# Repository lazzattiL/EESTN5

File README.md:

This repository is for any project I'll make during my studying period at E.E.S.T. N° 5 "2 de Abril". 
Triatlon robot will be added at some point of the competition to avoid others from stealing our code.
The following link is from the RadioFM project tinkercad model: https://www.tinkercad.com/things/35Wzm8qwek5-radio-fm-with-oled-display?sharecode=DG-30qTOyq2ryuBf1aKIaMlBNb57CfATmdjBPJIcnF0

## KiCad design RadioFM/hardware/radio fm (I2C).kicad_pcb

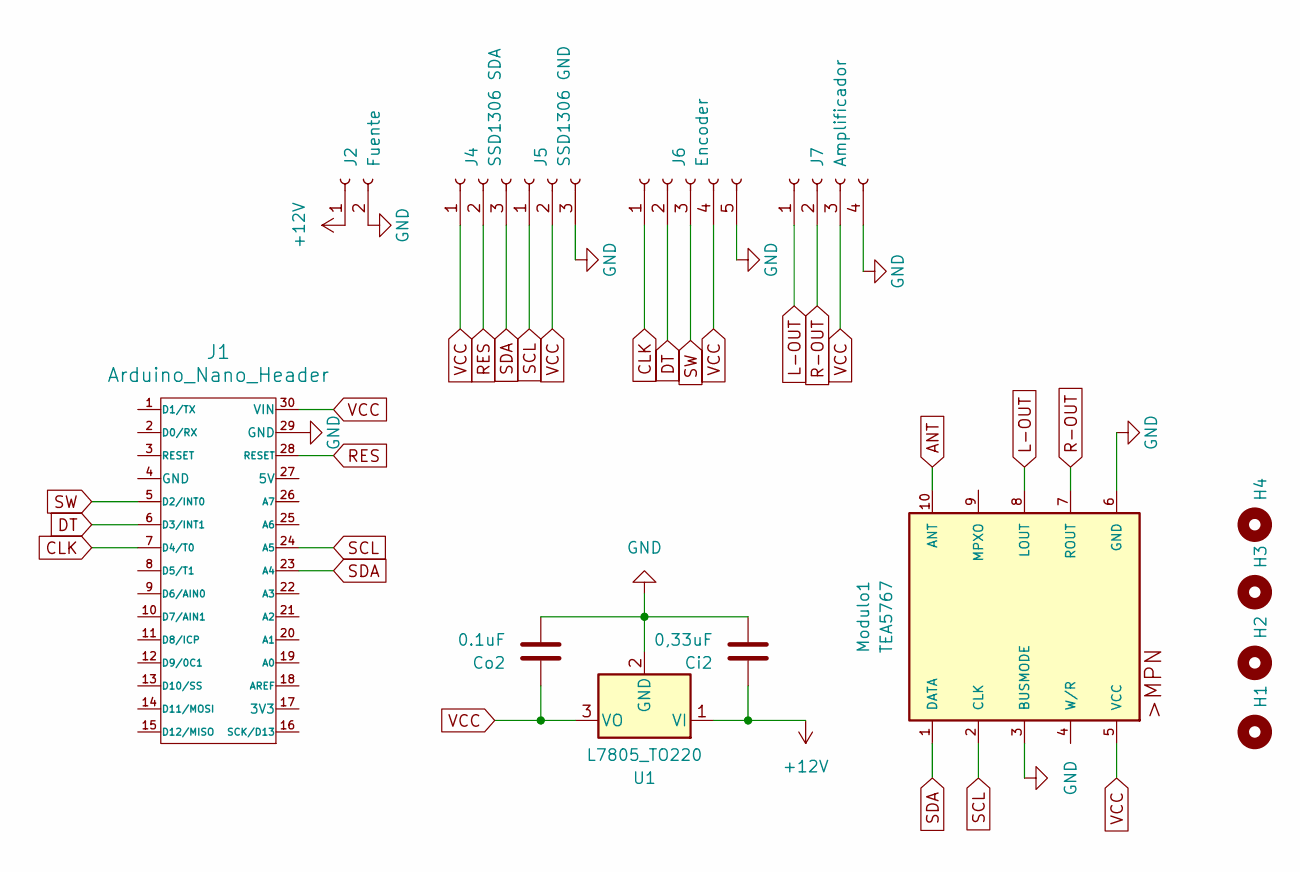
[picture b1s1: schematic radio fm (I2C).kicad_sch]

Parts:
Ci2: 0,33uF; C_Disc_D5.0mm_W2.5mm_P5.00mm
Co2: 0.1uF; C_Disc_D5.0mm_W2.5mm_P5.00mm
H1, H2, H3, H4: Mounting_Hole; hole_2mm
J1: Arduino_Nano_Header; Arduino_Nano
J2: Fuente; Molex_KK-254_AE-6410-02A_1x02_P2.54mm_Vertical
J4: SSD1306 SDA; Molex_KK-254_AE-6410-03A_1x03_P2.54mm_Vertical
J5: SSD1306 GND; Molex_KK-254_AE-6410-03A_1x03_P2.54mm_Vertical
J6: Encoder; Molex_KK-254_AE-6410-05A_1x05_P2.54mm_Vertical
J7: Amplificador; Molex_KK-254_AE-6410-04A_1x04_P2.54mm_Vertical
Modulo1: TEA5767; MPN TEA5767
U1: L7805_TO220; TO-220-3_Vertical

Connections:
+12V: Ci2.1, J2.1, U1.1 (VI)
ANT: Modulo1.10 (ANT)
CLK: J1.7 (D4/T0), J6.1
DT: J1.6 (D3/INT1), J6.2
GND: Ci2.2, Co2.2, J1.29 (GND), J2.2, J5.3, J6.5, J7.4, Modulo1.3 (BUSMODE), Modulo1.6 (GND), U1.2 (GND)
L-OUT: J7.1, Modulo1.8 (LOUT)
R-OUT: J7.2, Modulo1.7 (ROUT)
RES: J1.28 (RESET), J4.2
SCL: J1.24 (A5), J5.1, Modulo1.2 (CLK)
SDA: J1.23 (A4), J4.3, Modulo1.1 (DATA)
SW: J1.5 (D2/INT0), J6.3
VCC: Co2.1, J1.30 (VIN), J4.1, J5.2, J6.4, J7.3, Modulo1.5 (VCC), U1.3 (VO)

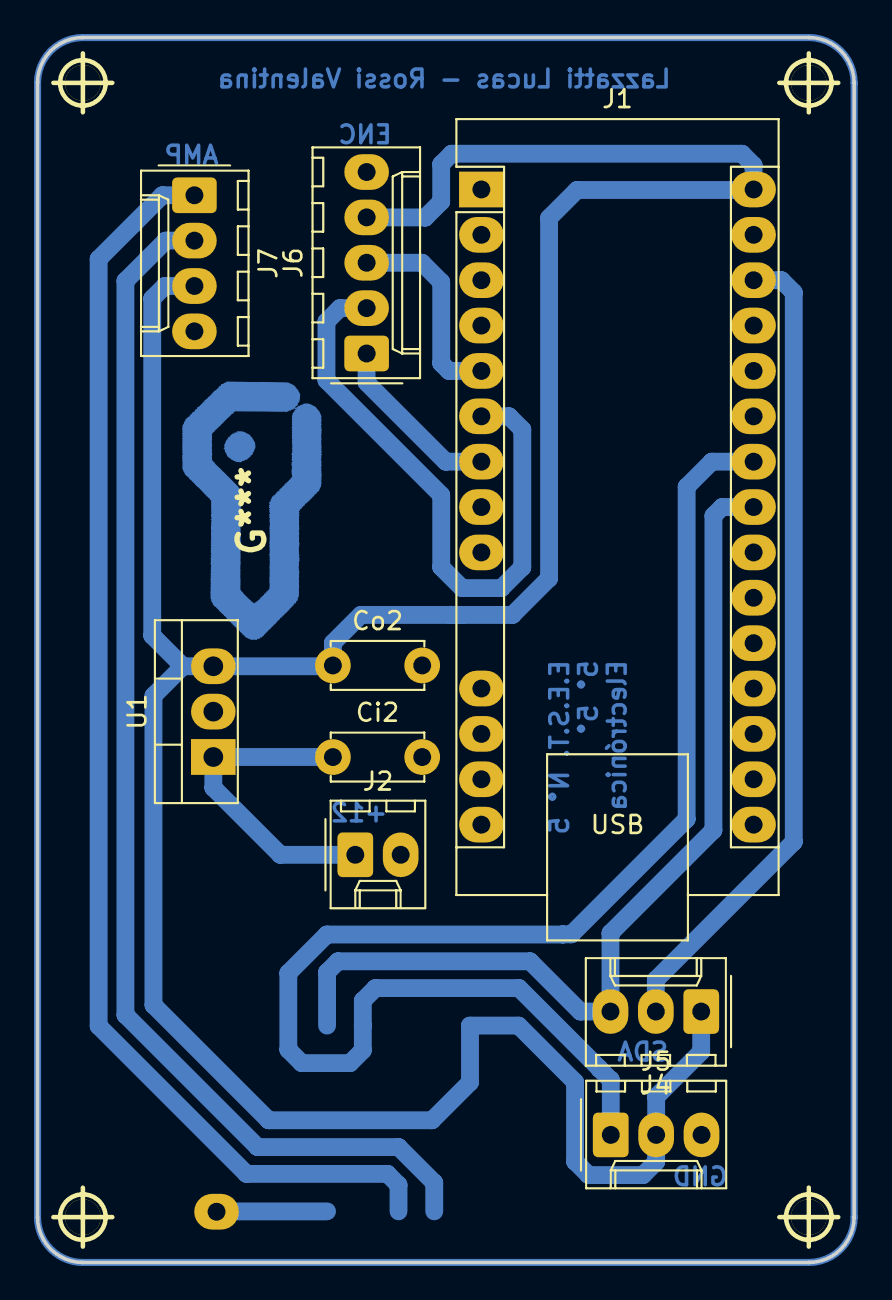
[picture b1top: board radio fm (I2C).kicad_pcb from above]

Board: 2 copper layers, 45.7 x 68.6 mm, 14 parts (1 on the bottom side), 11 nets.

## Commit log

2024-05-26 Create RadioFM
2024-05-26 Create scr
2024-05-26 Create xd
